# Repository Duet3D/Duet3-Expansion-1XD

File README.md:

# Duet 3 Expansion 1XD
Hardware information for the Duet 3 Expansion 1XD. This is a CAN-FD connected expansion board for the [Duet 3 Mainboard](https://www.duet3d.com/Duet3Mainboard6HC) and [Duet 3 Mini 5+](https://www.duet3d.com/Duet3Mini5plus) that allows connection for a single external stepper driver and associated peripherals.

Product page is here: https://www.duet3d.com/Duet3Expansion1XD 

Documentation is here: https://docs.duet3d.com/Duet3D_hardware/Duet_3_family/Duet_3_Expansion_1XD

As always please discuss this on the Duet3d forum: https://forum.duet3d.com/

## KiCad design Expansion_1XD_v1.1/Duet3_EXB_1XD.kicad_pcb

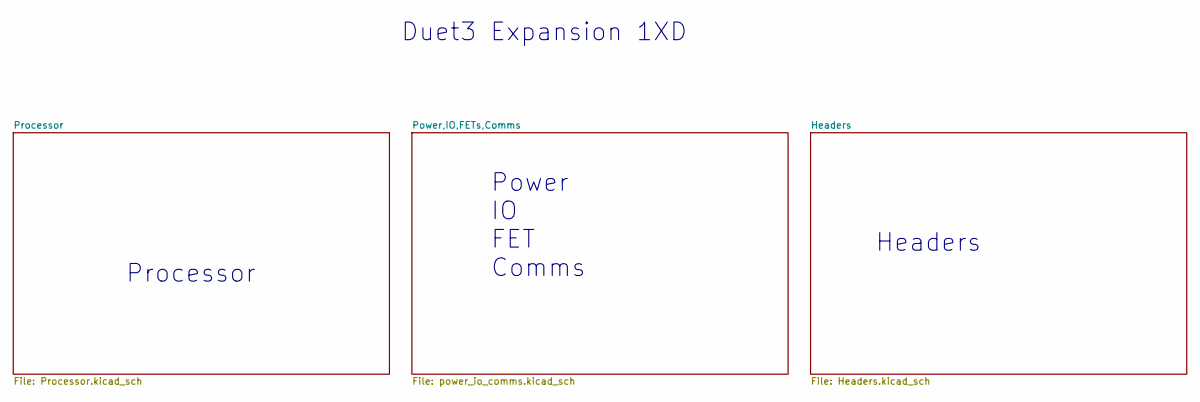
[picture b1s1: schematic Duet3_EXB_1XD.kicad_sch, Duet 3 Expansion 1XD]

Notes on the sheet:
Duet3 Expansion 1XD
Processor
Power IO FET Comms
Headers

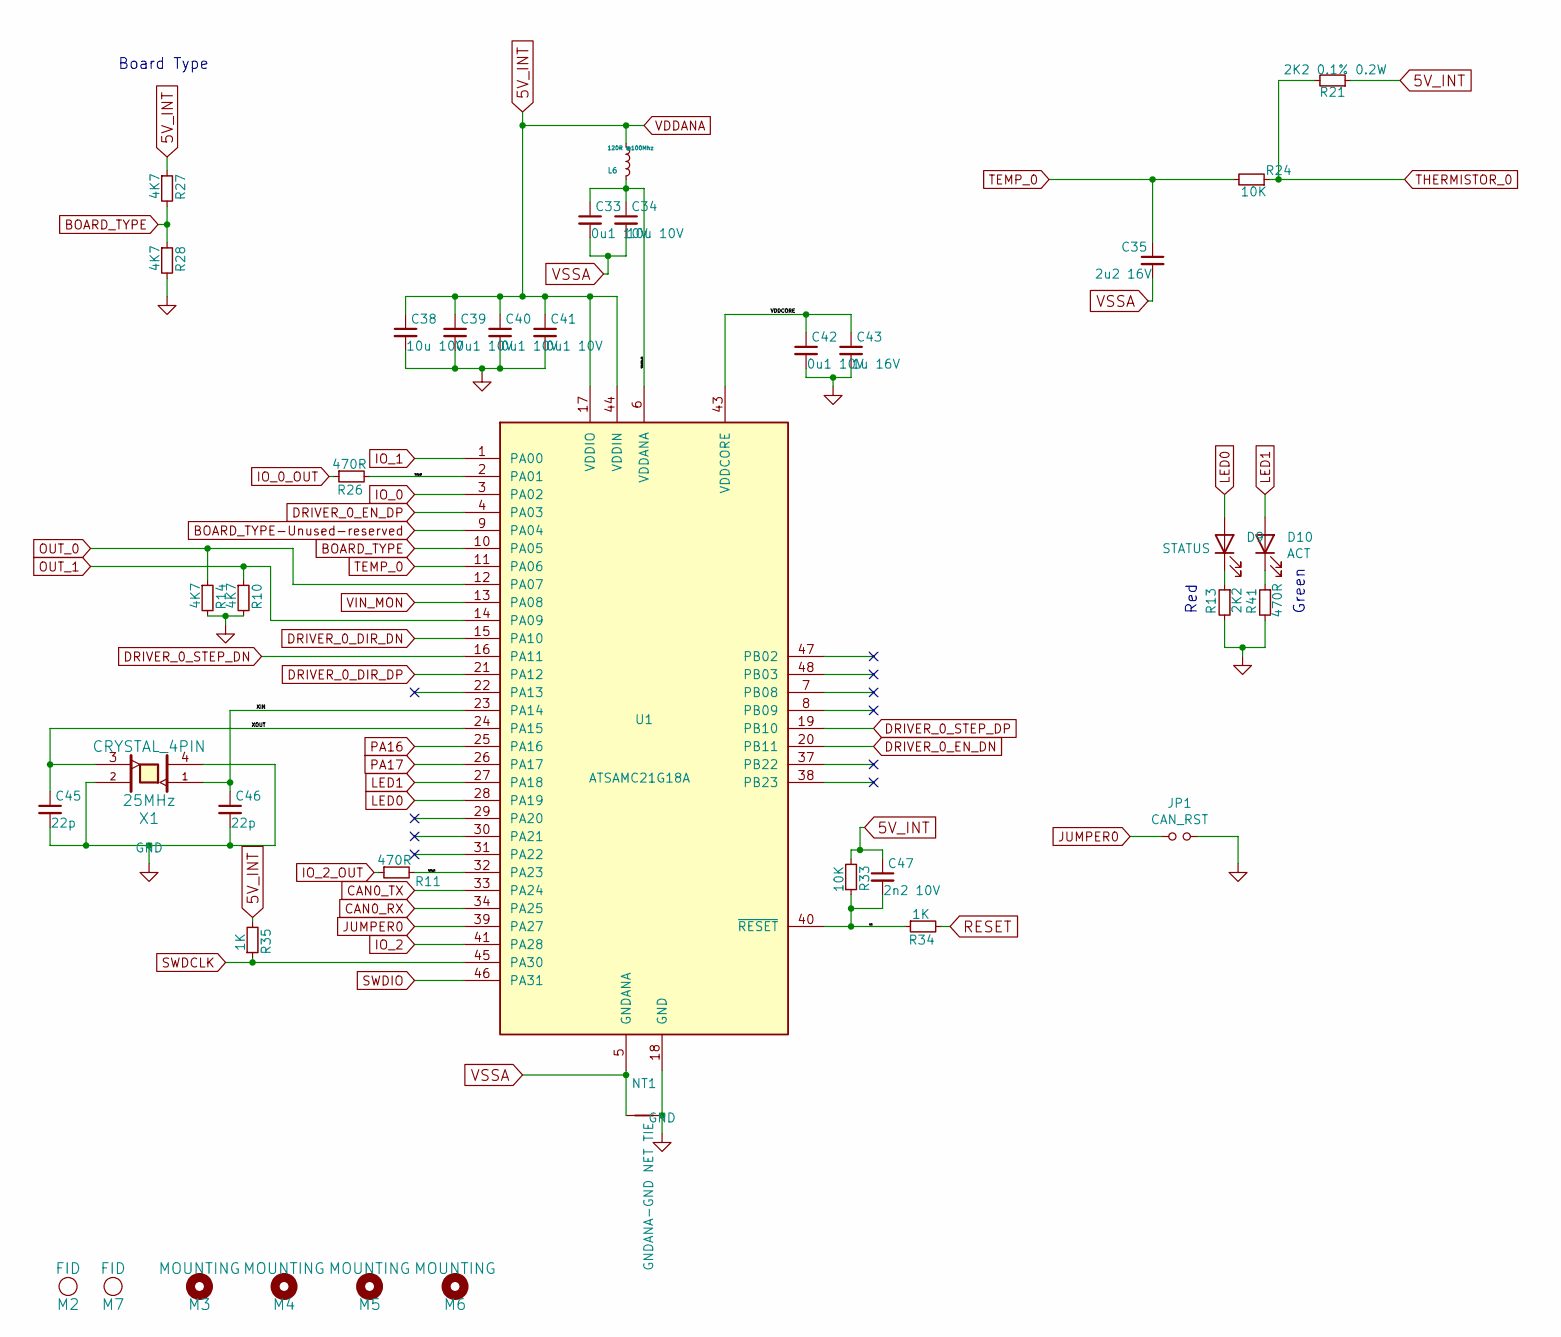
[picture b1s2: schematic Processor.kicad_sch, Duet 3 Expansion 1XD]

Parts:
C33, C39, C40, C41, C42: 0u1 10V; C_0402_1005Metric_Wbry; Part Number CL05B104KP5NNNC
C34, C38: 10u 10V; C_0805_2012Metric; Part Number GRM21BR71A106KA73K
C35: 2u2 16V; C_0402_1005Metric_Wbry; Part Number GRM155C81C225ME15D
C43: 1u 16V; C_0603_1608Metric_Wbry; Part Number CL10B105KO8NNNC
C45, C46: 22p; C_0402_1005Metric_Wbry; Part Number C0402C220J4GACTU
C47: 2n2 10V; C_0402_1005Metric_Wbry; Part Number 0402YC222KAT2A
D9: STATUS; LED_0603_1608Metric; Part Number 150060RS75000 or equivalent Red
D10: ACT; LED_0603_1608Metric; Part Number 150060VS75000 or equivalent Green
JP1: CAN_RST; PinHeader_1x02_P2.54mm_Vertical; Part Number 2 way pin header + Jumper
L6: 120R @100Mhz; L_0402_1005Metric; Part Number 7427927311 or similar
M2, M7: FID; Fiducial_1mm_Mask2mm; Part Number virtual component - DNP
M3, M4, M5, M6: MOUNTING; MountingHole_3.2mm_M3; Part Number virtual component - DNP
NT1: GNDANA-GND NET TIE; NetTie-2_SMD_Pad0.5mm; Part Number virtual component - DNP
R10, R14, R27, R28: 4K7; R_0402_1005Metric_Wbry; Part Number RK73H1ETTP4701F
R11, R26, R41: 470R; R_0402_1005Metric_Wbry; Part Number RK73H1ETTP4700F
R13: 2K2; R_0402_1005Metric_Wbry; Part Number RK73H1ETTP2201F
R21: 2K2 0.1% 0.2W; R_0603_1608Metric_Wbry; Part Number ERJ-PB3B2201V
R24, R33: 10K; R_0402_1005Metric_Wbry; Part Number RK73H1ETTP1002F
R34, R35: 1K; R_0402_1005Metric_Wbry; Part Number RK73H1ETTP1001F
U1: ATSAMC21G18A; QFN-48-1EP_7x7mm_P0.5mm_EP5.2x5.2mm_ThermalVias; Part Number ATSAMC21G18A-MU
X1: CRYSTAL_4PIN; Crystal_SMD_ECS-33B-4Pin_3.2x2.5mm; Part Number TSX-3225 25.0000MF10P

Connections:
5V_INT: C38.1, C39.1, C40.1, C41.1, C47.1, L6.1, R21.1, R27.1, R33.2, R35.2, U1.17 (VDDIO), U1.36 (VDDIO), U1.44 (VDDIN); also elsewhere on the board
/Processor/VDDANA_IN: C33.1, C34.1, L6.2, U1.6 (VDDANA)
/Processor/VDDCORE: C42.1, C43.1, U1.43 (VDDCORE)
/Processor/XIN: C46.1, U1.23 (PA14), X1.1
/Processor/XOUT: C45.1, U1.24 (PA15), X1.3
/Processor/io0out: R26.2, U1.2 (PA01)
/Processor/io2out: R11.2, U1.32 (PA23)
/Processor/rst: C47.2, R33.1, R34.1, U1.40 (~RESET)
BOARD_TYPE: R27.2, R28.1, U1.10 (PA05)
BOARD_TYPE-Unused-reserved: U1.9 (PA04)
CAN0_RX: U1.34 (PA25); also elsewhere on the board
CAN0_TX: U1.33 (PA24); also elsewhere on the board
DRIVER_0_DIR_DN: U1.15 (PA10); also elsewhere on the board
DRIVER_0_DIR_DP: U1.21 (PA12); also elsewhere on the board
DRIVER_0_EN_DN: U1.20 (PB11); also elsewhere on the board
DRIVER_0_EN_DP: U1.4 (PA03); also elsewhere on the board
DRIVER_0_STEP_DN: U1.16 (PA11); also elsewhere on the board
DRIVER_0_STEP_DP: U1.19 (PB10); also elsewhere on the board
GND: C38.2, C39.2, C40.2, C41.2, C42.2, C43.2, C45.2, C46.2, JP1.2, NT1.2, R10.2, R13.2, R14.2, R28.2, R41.2, U1.18 (GND), U1.35 (GND), U1.42 (GND), U1.49 (GND), X1.2, X1.4; also elsewhere on the board
IO_0: U1.3 (PA02); also elsewhere on the board
IO_0_OUT: R26.1; also elsewhere on the board
IO_1: U1.1 (PA00); also elsewhere on the board
IO_2: U1.41 (PA28); also elsewhere on the board
IO_2_OUT: R11.1; also elsewhere on the board
JUMPER0: JP1.1, U1.39 (PA27)
LED0: D9.2 (A), U1.28 (PA19)
LED1: D10.2 (A), U1.27 (PA18)
unnamed: D9.1 (K), R13.1
unnamed: D10.1 (K), R41.1
OUT_0: R14.1, U1.12 (PA07); also elsewhere on the board
OUT_1: R10.1, U1.14 (PA09); also elsewhere on the board
PA16: U1.25 (PA16); also elsewhere on the board
PA17: U1.26 (PA17); also elsewhere on the board
RESET: R34.2; also elsewhere on the board
SWDCLK: R35.1, U1.45 (PA30); also elsewhere on the board
SWDIO: U1.46 (PA31); also elsewhere on the board
TEMP_0: C35.1, R24.2, U1.11 (PA06)
THERMISTOR_0: R21.2, R24.1; also elsewhere on the board
VIN_MON: U1.13 (PA08); also elsewhere on the board
VSSA: C33.2, C34.2, C35.2, NT1.1, U1.5 (GNDANA); also elsewhere on the board

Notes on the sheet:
Board Type
Green
Red

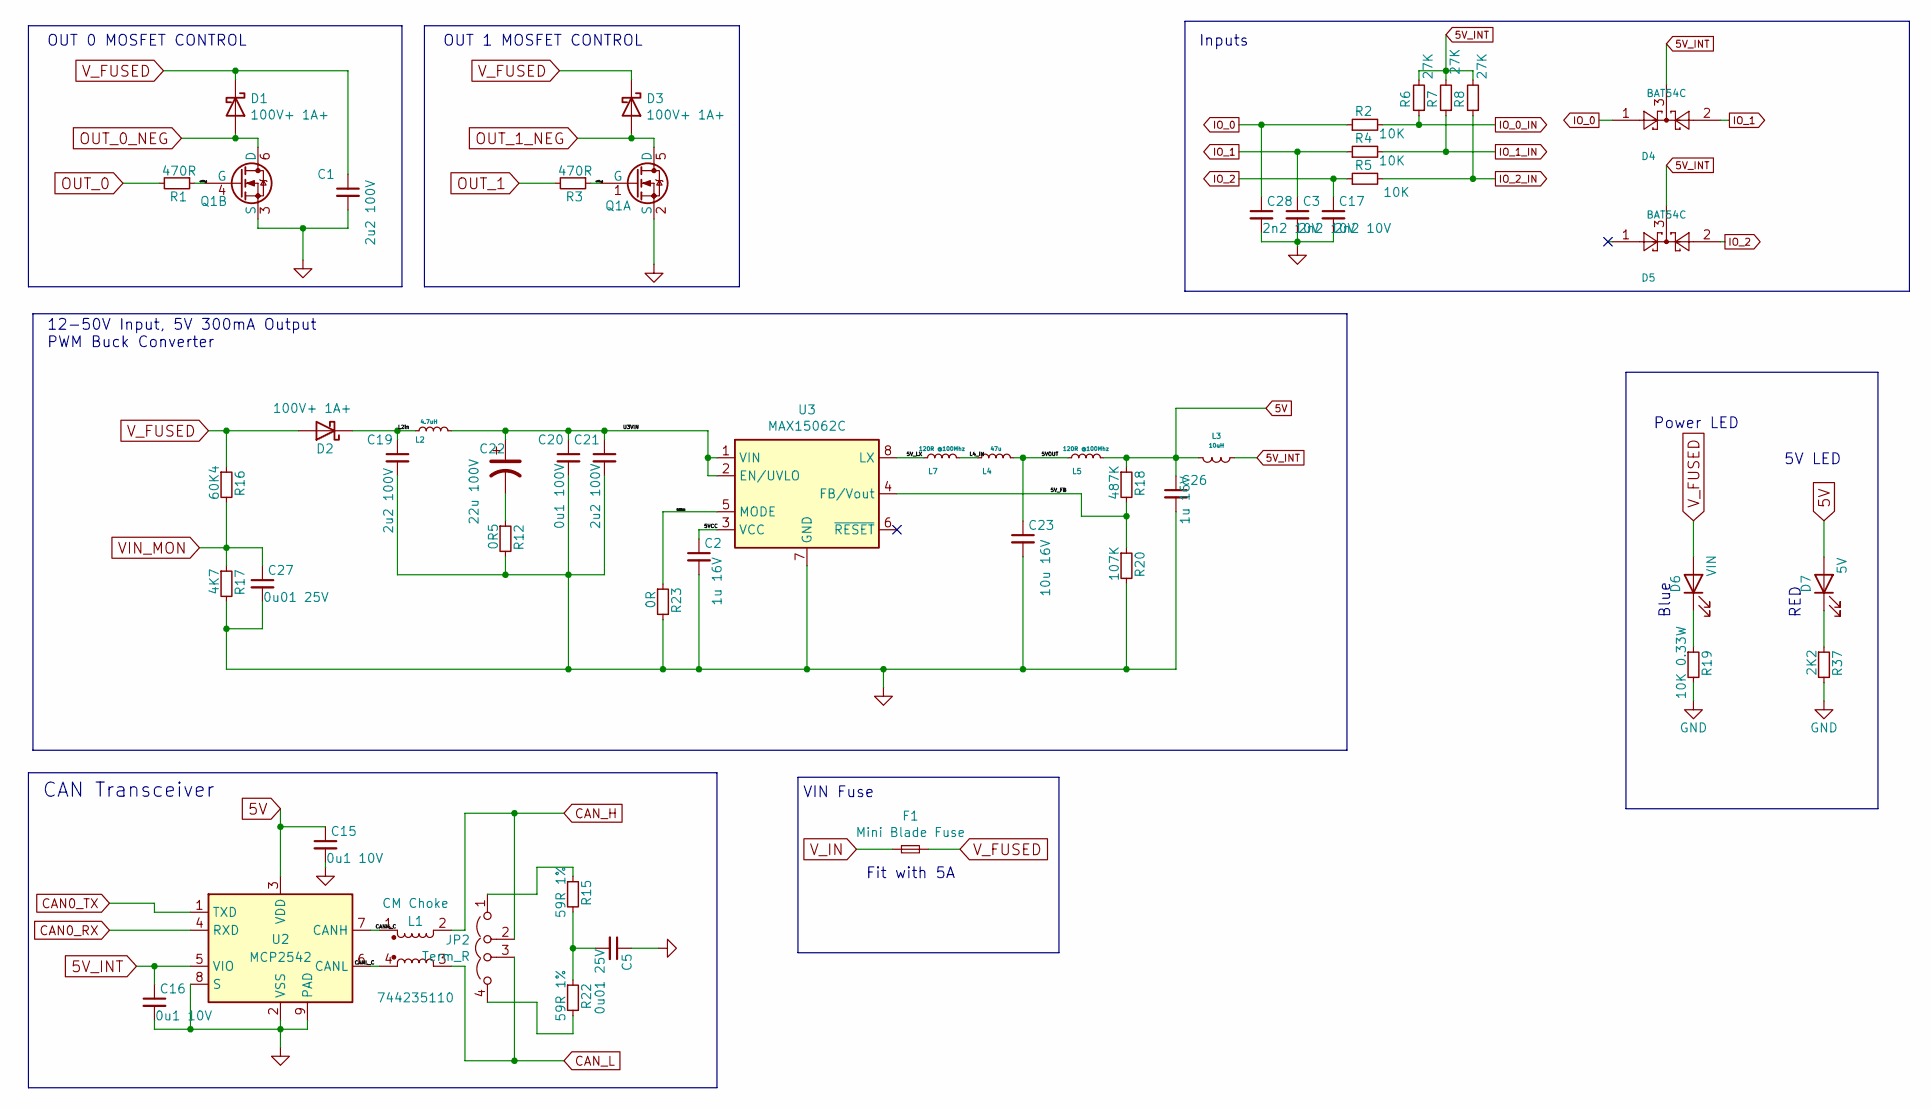
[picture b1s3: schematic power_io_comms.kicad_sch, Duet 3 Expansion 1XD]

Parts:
C1, C19, C21: 2u2 100V; C_1210_3225Metric; Part Number CL32B225KCJSNNE
C2: 1u 16V; C_0603_1608Metric_Wbry; Rating 35V +; Part Number CL10B105KO8NNNC
C3, C17, C28: 2n2 10V; C_0402_1005Metric_Wbry; Part Number 0402YC222KAT2A
C5, C27: 0u01 25V; C_0402_1005Metric_Wbry; Part Number TMK105B7103KV-F
C15, C16: 0u1 10V; C_0402_1005Metric_Wbry; Part Number CL05B104KP5NNNC
C20: 0u1 100V; C_0603_1608Metric_Wbry; Part Number CL10B104KC8NNNC
C22: 22u 100V; CP_Elec_8x10; Part Number EEE-2AA220UP or similar
C23: 10u 16V; C_1206_3216Metric; Rating 6.3V or higher, similar X7R; Part Number CL31B106MOHNNNE
C26: 1u 16V; C_0603_1608Metric_Wbry; Rating 10V+; Part Number CL10B105KO8NNNC
D1, D2, D3: 100V+ 1A+; D_SMF; Part Number SS1FH10-M3/H or similar
D4, D5: BAT54C; SOT-23; Part Number BAT54CLT1G
D6: VIN; LED_0603_1608Metric; Part Number 150060BS75000 or equiv Blue
D7: 5V; LED_0603_1608Metric; Part Number 150060RS75000 or equivalent Red
F1: Mini Blade Fuse; MCCQ-122-minibladefuseholder; Part Number Fit with 5A Fuse
JP2: Term_R; PinHeader_1x04_P2.54mm_Vertical; Part Number 4 way pin header + 2xJumpers
L1: CM Choke; Wurth_CM_Choke_1812_744235nnn; Part Number 744235110
L2: 4.7uH; L_0805_2012Metric; Part Number MBKK2012T4R7M or CB2012T4R7M or similar
L3: 10uH; L_1008_2512Metric; Part Number e.g. CBC2518T100M
L4: 47u; L_Taiyo-Yuden_NR-40xx; Part Number NRS4018T470MDGJ or similar
L5, L7: 120R @100Mhz; L_0402_1005Metric; Part Number 7427927311 or similar
Q1: Q_DUAL_NMOS; Fairchild_DualPower33-6_3x3mm; Part Number DMT6018LDR-13-ND
R1, R3: 470R; R_0402_1005Metric_Wbry; Part Number RK73H1ETTP4700F
R2, R4, R5: 10K; R_0402_1005Metric_Wbry; Part Number RK73H1ETTP1002F
R6, R7, R8: 27K; R_0402_1005Metric_Wbry; Part Number RK73H1ETTP2702F
R12: 0R5; R_0402_1005Metric_Wbry; Part Number CSR0402FKR500
R15, R22: 59R 1%; R_0402_1005Metric_Wbry; Part Number RK73H1ETTP59R0F
R16: 60K4; R_0402_1005Metric_Wbry; Part Number ERJ-2RKF6042X
R17: 4K7; R_0402_1005Metric_Wbry; Part Number RK73H1ETTP4701F
R18: 487K; R_0402_1005Metric_Wbry; Part Number RK73H1ETTP4873F
R19: 10K 0.33W; R_0805_2012Metric; Part Number CRGH0805F10K
R20: 107K; R_0402_1005Metric_Wbry; Part Number RK73H1ETTP1073F
R23: 0R; R_0402_1005Metric_Wbry; Part Number CR0402-J/-000GLF
R37: 2K2; R_0402_1005Metric_Wbry; Part Number RK73H1ETTP2201F
U2: MCP2542; DFN-8-1EP_3x2mm_P0.5mm_EP1.3x1.5mm; Part Number MCP2542FDT-E/MNY
U3: MAX15062C; DFN-8_2x2mm_P0.5mm; Part Number MAX15062CATA+T

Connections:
5V: C15.1, C26.1, D7.2 (A), L3.1 (A), L5.2, R18.1, U2.3 (VDD); also elsewhere on the board
5V_INT: C16.1, D4.3, D5.3, L3.2 (B), R6.2, R7.2, R8.2, U2.5 (VIO); also elsewhere on the board
/Power,IO,FETs,Comms/5VCC: C2.1, U3.3 (VCC)
/Power,IO,FETs,Comms/5VMODE: R23.1, U3.5 (MODE)
/Power,IO,FETs,Comms/5VOUT: C23.1, L4.2, L5.1
/Power,IO,FETs,Comms/5V_FB: R18.2, R20.1, U3.4 (FB/Vout)
/Power,IO,FETs,Comms/5V_LX: L7.1, U3.8 (LX)
/Power,IO,FETs,Comms/CANH_C: L1.1, U2.7 (CANH)
/Power,IO,FETs,Comms/CANL_C: L1.4, U2.6 (CANL)
/Power,IO,FETs,Comms/L2in: C19.1, D2.1 (K), L2.1
/Power,IO,FETs,Comms/L4_IN: L4.1, L7.2
/Power,IO,FETs,Comms/U3VIN: C20.1, C21.1, C22.1, L2.2, U3.1 (VIN), U3.2 (EN/UVLO)
/Power,IO,FETs,Comms/out0_g: Q1.4 (G), R1.1
/Power,IO,FETs,Comms/out1_g: Q1.1 (G), R3.1
CAN0_RX: U2.4 (RXD); also elsewhere on the board
CAN0_TX: U2.1 (TXD); also elsewhere on the board
CAN_H: JP2.2 (C), L1.2; also elsewhere on the board
CAN_L: JP2.3 (C), L1.3; also elsewhere on the board
GND: C1.2, C2.2, C3.2, C5.1, C15.2, C16.2, C17.2, C19.2, C20.2, C21.2, C23.2, C26.2, C27.2, C28.2, Q1.2 (S), Q1.3 (S), R12.2, R17.2, R19.2, R20.2, R23.2, R37.2, U2.2 (VSS), U2.8 (S), U2.9 (PAD), U3.7 (GND); also elsewhere on the board
IO_0: C28.1, D4.1, R2.1; also elsewhere on the board
IO_0_IN: R2.2, R6.1; also elsewhere on the board
IO_1: C3.1, D4.2, R4.1; also elsewhere on the board
IO_1_IN: R4.2, R7.1; also elsewhere on the board
IO_2: C17.1, D5.2, R5.1; also elsewhere on the board
IO_2_IN: R5.2, R8.1; also elsewhere on the board
unnamed: C5.2, R15.2, R22.1
unnamed: C22.2, R12.1
unnamed: D6.1 (K), R19.1
unnamed: D7.1 (K), R37.1
unnamed: JP2.1 (A), R15.1
unnamed: JP2.4 (B), R22.2
OUT_0: R1.2; also elsewhere on the board
OUT_0_NEG: D1.2 (A), Q1.6 (D); also elsewhere on the board
OUT_1: R3.2; also elsewhere on the board
OUT_1_NEG: D3.2 (A), Q1.5 (D); also elsewhere on the board
VIN_MON: C27.1, R16.2, R17.1; also elsewhere on the board
V_FUSED: C1.1, D1.1 (K), D2.2 (A), D3.1 (K), D6.2 (A), F1.2, R16.1; also elsewhere on the board
V_IN: F1.1; also elsewhere on the board

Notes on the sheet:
RED
OUT 0 MOSFET CONTROL
12-50V Input, 5V 300mA Output PWM Buck Converter
OUT 1 MOSFET CONTROL
VIN Fuse
Inputs
CAN Transceiver
Power LED
Fit with 5A
Blue
5V LED

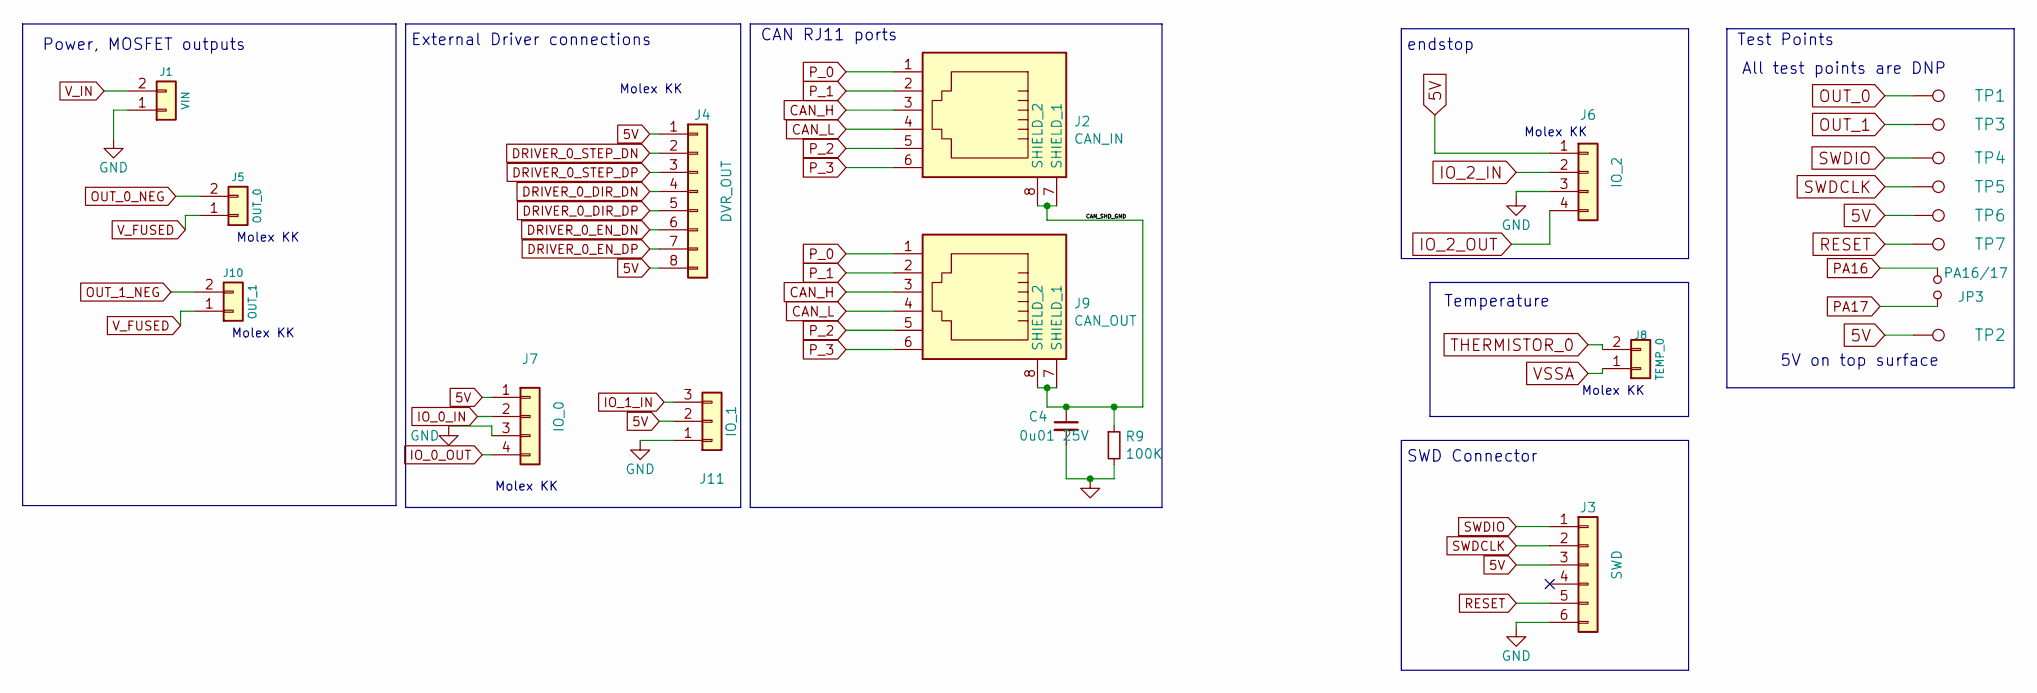
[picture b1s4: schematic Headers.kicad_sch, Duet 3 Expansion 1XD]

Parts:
C4: 0u01 25V; C_0402_1005Metric_Wbry; Part Number TMK105B7103KV-F
J1: VIN; JST_VH_B2P-VH_1x02_P3.96mm_Vertical; Part Number B2P-VH(LF)(SN)
J2: CAN_IN; RJ11_6P6C_half_shield; Part Number 615006143421
J3: SWD; JST_ZH_1x06_P1.5_B6B-ZR-SM4-TF; Part Number DNP
J4: DVR_OUT; Molex_KK-254_AE-6410-08A_1x08_P2.54mm_Vertical; Part Number 61900811121
J5: OUT_0; Molex_KK-254_AE-6410-02A_1x02_P2.54mm_Vertical; Part Number 61900211121
J6: IO_2; Molex_KK-254_AE-6410-04A_1x04_P2.54mm_Vertical; Part Number 61900411121
J7: IO_0; Molex_KK-254_AE-6410-04A_1x04_P2.54mm_Vertical; Part Number 61900411121
J8: TEMP_0; Molex_KK-254_AE-6410-02A_1x02_P2.54mm_Vertical; Part Number 61900211121
J9: CAN_OUT; RJ11_6P6C_half_shield; Part Number 615006143421
J10: OUT_1; Molex_KK-254_AE-6410-02A_1x02_P2.54mm_Vertical; Part Number 61900211121
J11: IO_1; Molex_KK-254_AE-6410-03A_1x03_P2.54mm_Vertical; Part Number 61900311121
JP3: PA16/17; PinHeader_1x02_P2.54mm_Vertical; Part Number DNP
R9: 100K; R_0402_1005Metric_Wbry; Part Number RK73H1ETTP1003F
TP1: OUT_0; TestPoint_Pad_D2.0mm; Part Number virtual component - DNP
TP2, TP6: 5V; TestPoint_Pad_D2.0mm; Part Number virtual component - DNP
TP3: OUT_1; TestPoint_Pad_D2.0mm; Part Number virtual component - DNP
TP4: SWDIO; TestPoint_Pad_D2.0mm; Part Number virtual component - DNP
TP5: SWDCLK; TestPoint_Pad_D2.0mm; Part Number virtual component - DNP
TP7: RST; TestPoint_Pad_D2.0mm; Part Number virtual component - DNP

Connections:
5V: J3.3, J4.1, J4.8, J6.1, J7.1, J11.2, TP2.1, TP6.1; also elsewhere on the board
/Headers/CAN_SHD_GND: C4.1, J2.7 (SHIELD_1), J2.8 (SHIELD_2), J9.7 (SHIELD_1), J9.8 (SHIELD_2), R9.1
CAN_H: J2.3, J9.3; also elsewhere on the board
CAN_L: J2.4, J9.4; also elsewhere on the board
DRIVER_0_DIR_DN: J4.4; also elsewhere on the board
DRIVER_0_DIR_DP: J4.5; also elsewhere on the board
DRIVER_0_EN_DN: J4.6; also elsewhere on the board
DRIVER_0_EN_DP: J4.7; also elsewhere on the board
DRIVER_0_STEP_DN: J4.2; also elsewhere on the board
DRIVER_0_STEP_DP: J4.3; also elsewhere on the board
GND: C4.2, J1.1, J3.6, J6.3, J7.3, J11.1, R9.2; also elsewhere on the board
IO_0_IN: J7.2; also elsewhere on the board
IO_0_OUT: J7.4; also elsewhere on the board
IO_1_IN: J11.3; also elsewhere on the board
IO_2_IN: J6.2; also elsewhere on the board
IO_2_OUT: J6.4; also elsewhere on the board
OUT_0: TP1.1; also elsewhere on the board
OUT_0_NEG: J5.2; also elsewhere on the board
OUT_1: TP3.1; also elsewhere on the board
OUT_1_NEG: J10.2; also elsewhere on the board
PA16: JP3.2; also elsewhere on the board
PA17: JP3.1; also elsewhere on the board
P_0: J2.1, J9.1
P_1: J2.2, J9.2
P_2: J2.5, J9.5
P_3: J2.6, J9.6
RESET: J3.5, TP7.1; also elsewhere on the board
SWDCLK: J3.2, TP5.1; also elsewhere on the board
SWDIO: J3.1, TP4.1; also elsewhere on the board
THERMISTOR_0: J8.2; also elsewhere on the board
VSSA: J8.1; also elsewhere on the board
V_FUSED: J5.1, J10.1; also elsewhere on the board
V_IN: J1.2; also elsewhere on the board

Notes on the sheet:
Molex KK
Power, MOSFET outputs
CAN RJ11 ports
All test points are DNP
5V on top surface
Test Points
SWD Connector
External Driver connections
Temperature
endstop

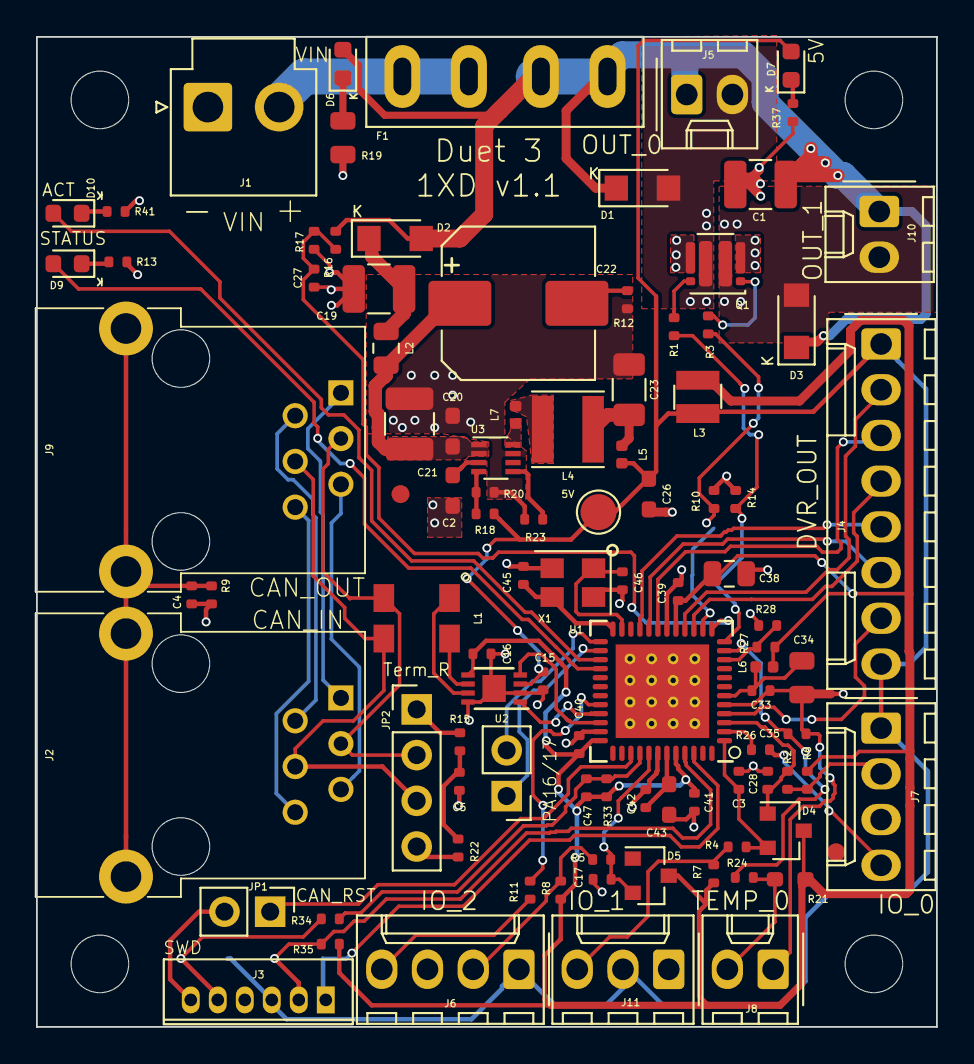
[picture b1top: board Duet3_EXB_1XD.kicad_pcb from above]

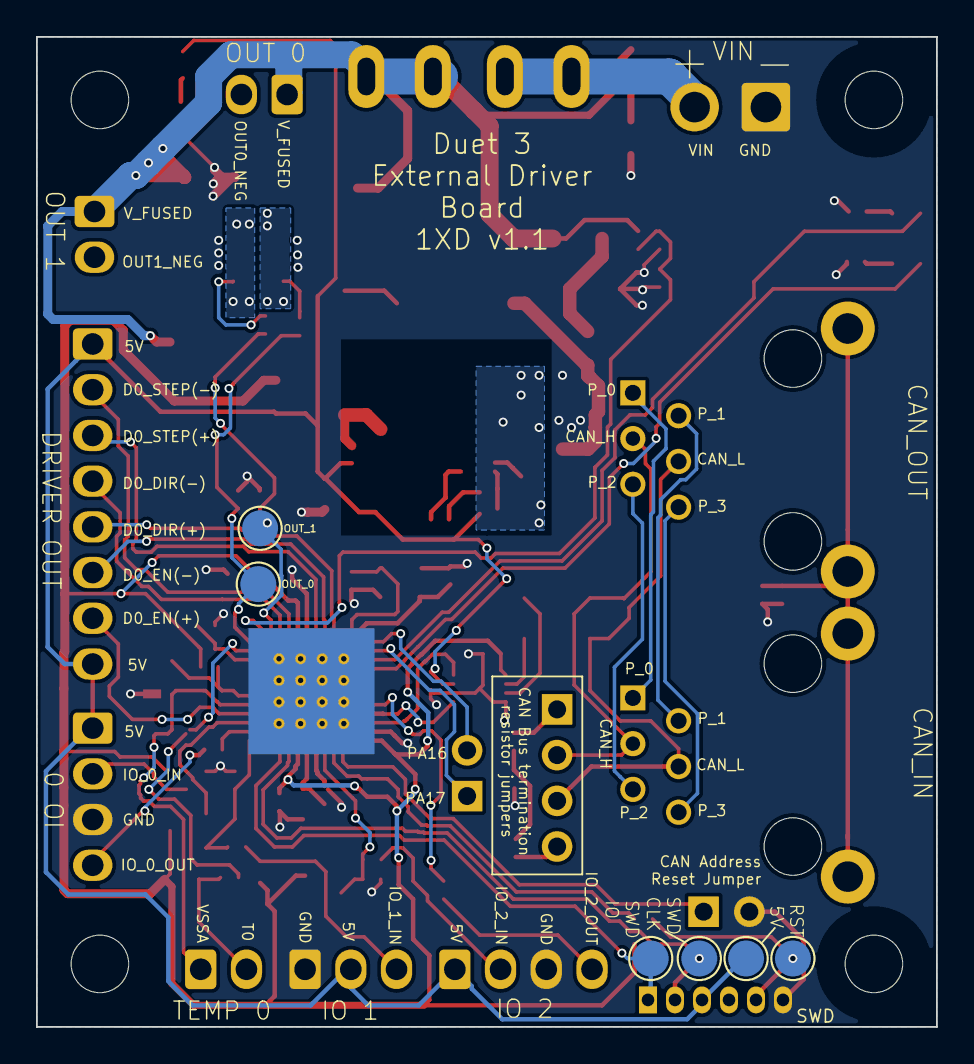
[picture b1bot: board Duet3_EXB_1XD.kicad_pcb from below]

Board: 2 copper layers, 50.0 x 55.0 mm, 110 parts (6 on the bottom side), 72 nets.

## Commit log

2020-06-15 Schematic, STEP and documentation images
2020-06-22 Added the iBOM for the 1XD board
2020-11-11 v1.0
2020-11-11 new image
2020-11-11 Updated links
2021-12-23 Add Duet 3 License
2023-11-13 v1.1 Source files
2026-06-17 Replaced x0rtrunks with droftarts
